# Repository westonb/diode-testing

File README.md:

# diode-testing
A low cost and open source circuit for the reverse recovery charge testing of small signal diodes

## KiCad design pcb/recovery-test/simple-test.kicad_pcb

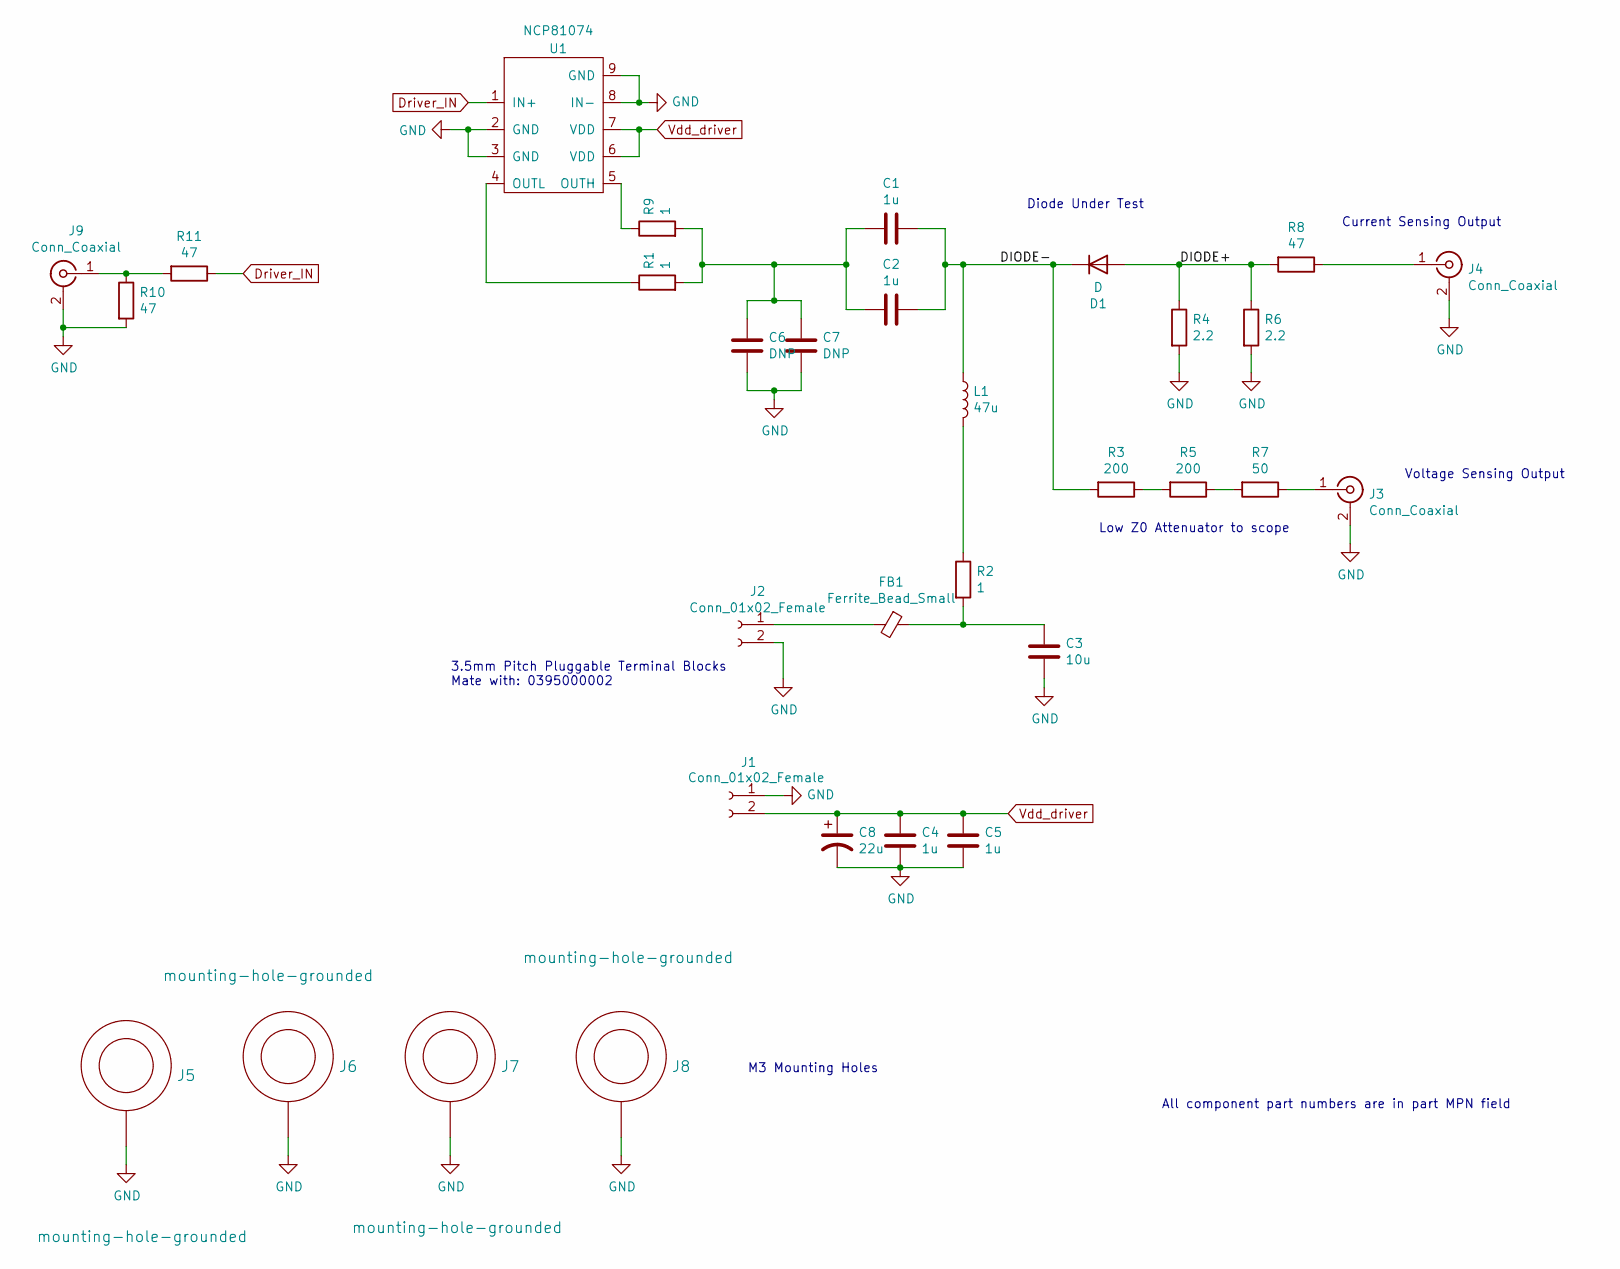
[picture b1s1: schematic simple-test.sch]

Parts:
C1, C2, C4, C5: 1u; C_0402_1005Metric; MPN CGB2A1X5R1E105K033BC
C3: 10u; C_0805_2012Metric; MPN GRM21BR61E106KA73L
C6, C7: DNP; C_0402_1005Metric
C8: 22u; CP_Elec_5x5.8; MPN UUD1V220MCL1GS
D1: D; D_SOD-323
FB1: Ferrite_Bead_Small; L_0805_2012Metric; MPN 2508052027Y1
J1, J2: Conn_01x02_Female; Terminal-block-plug_2x1_3.5mm-pitch; MPN 0395021002
J3, J4, J9: Conn_Coaxial; SMA_Molex_73251-1153_EdgeMount_Horizontal; MPN 0732511151
J5, J6, J7, J8: mounting-hole-grounded; M3-tight-fit-socket-head
L1: 47u; L_1210_3225Metric; MPN ADL3225V-470MT-TL000
R1, R9: 1; R_0402_1005Metric; MPN RC0402FR-071RL
R2: 1; R_0805_2012Metric; MPN RC0805JR-071RL
R3, R5: 200; R_0402_1005Metric; MPN PFR05S-201-FNH
R4, R6: 2.2; R_0402_1005Metric; MPN RC0402FR-072R2L
R7: 50; R_0402_1005Metric; MPN RN731ETTP50R0F50
R8, R11: 47; R_0402_1005Metric; MPN RMCF0402FT47R0
R10: 47; R_1206_3216Metric; MPN RC1206FR-0747RL
U1: NCP81074; DFN-8-1EP_2x2mm_P0.5mm_EP0.9x1.3mm; MPN NCP81074AMNTBG

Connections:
/DIODE+: D1.2 (A), R4.1, R6.1, R8.2
/DIODE-: C1.1, C2.1, D1.1 (K), L1.1, R3.2
Driver_IN: R11.1, U1.1 (IN+)
GND: C3.2, C4.2, C5.2, C6.2, C7.2, C8.2, J1.1, J2.2, J3.2 (Ext), J4.2 (Ext), J5.1, J6.1, J7.1, J8.1, J9.2 (Ext), R4.2, R6.2, R10.2, U1.2 (GND), U1.3 (GND), U1.8 (IN-), U1.9 (GND)
unnamed: C1.2, C2.2, C6.1, C7.1, R1.2, R9.2
unnamed: C3.1, FB1.1, R2.2
unnamed: FB1.2, J2.1
unnamed: J3.1 (In), R7.1
unnamed: J4.1 (In), R8.1
unnamed: J9.1 (In), R10.1, R11.2
unnamed: L1.2, R2.1
unnamed: R1.1, U1.4 (OUTL)
unnamed: R3.1, R5.2
unnamed: R5.1, R7.2
unnamed: R9.1, U1.5 (OUTH)
Vdd_driver: C4.1, C5.1, C8.1, J1.2, U1.6 (VDD), U1.7 (VDD)

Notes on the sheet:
Low Z0 Attenuator to scope
Diode Under Test
Current Sensing Output
Voltage Sensing Output
M3 Mounting Holes
3.5mm Pitch Pluggable Terminal Blocks Mate with: 0395000002
All component part numbers are in part MPN field

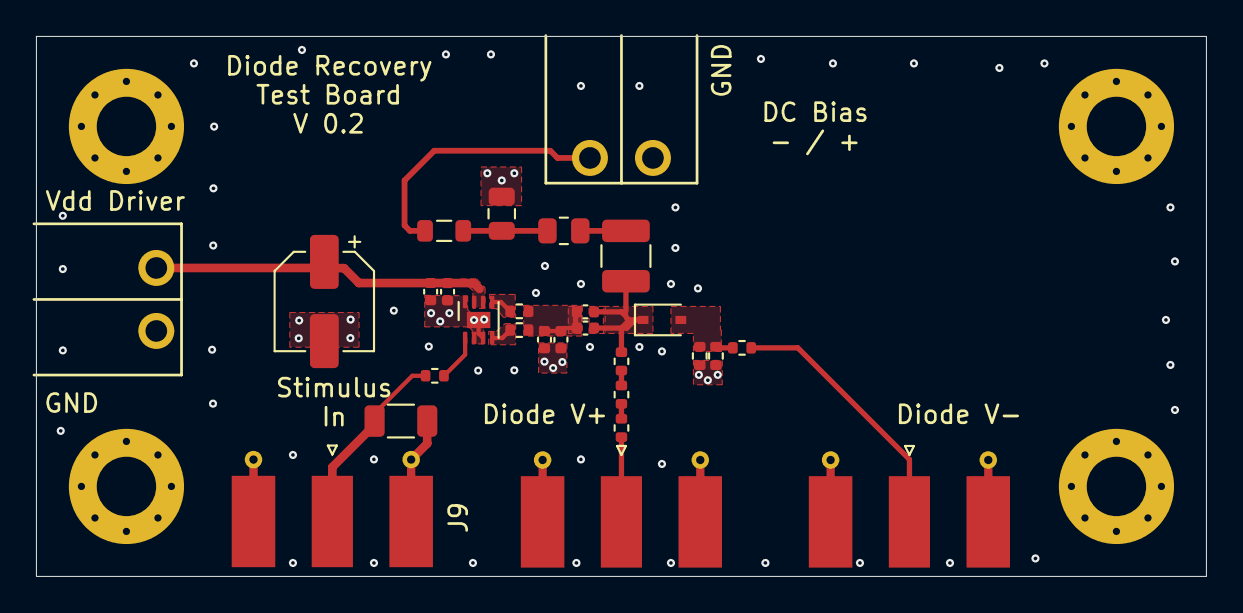
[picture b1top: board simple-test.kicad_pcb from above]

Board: 4 copper layers, 65.0 x 30.0 mm, 32 parts (0 on the bottom side), 16 nets.

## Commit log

2021-10-04 added project files
